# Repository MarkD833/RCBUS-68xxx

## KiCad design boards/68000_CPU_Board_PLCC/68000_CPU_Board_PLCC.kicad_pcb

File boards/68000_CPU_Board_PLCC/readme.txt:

DTACK Circuit:
==============
Silkscreen: It's 1,2,3 or 4 clocks NOT 2,4,8 or 16!

RCBus /RD & /WR signals:
========================
Possibly don't use /UDS or /LDS to gate the /RD or /WR signals.
Disconnect U4-8 from U5-13.
Connect U5-13 to +5V.

68000 R/W signal:
=================
This needs to go on the backplane as the 68681 needs the R/W signal
set before /CS is active.
Connect 68000 R/W signal (pin 9) to RCBus pin 35 (temporary fix).

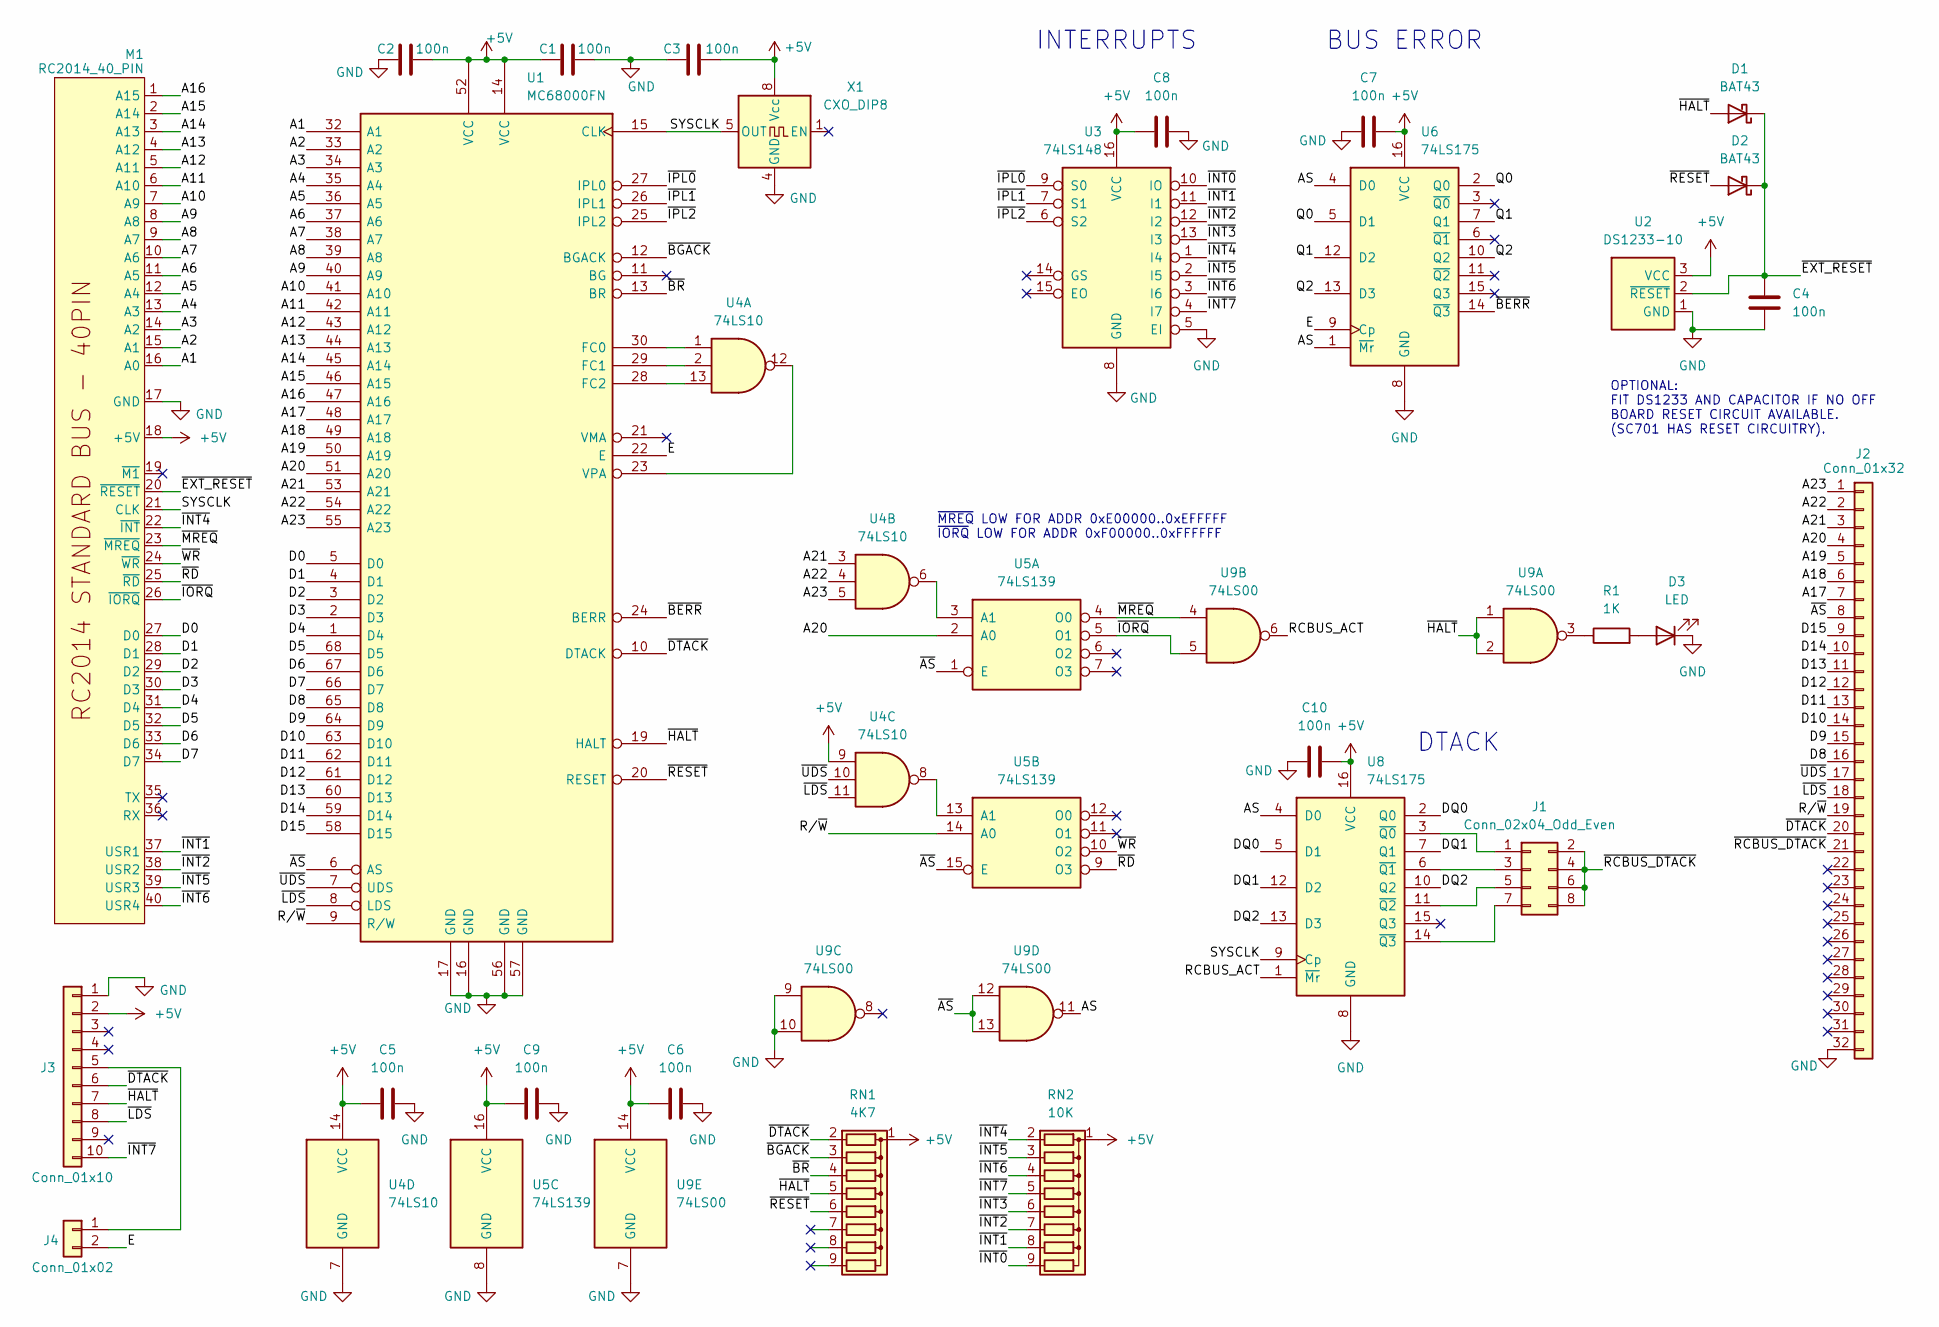
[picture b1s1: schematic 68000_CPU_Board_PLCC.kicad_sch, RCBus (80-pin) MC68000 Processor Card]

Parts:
C1, C2, C3, C4, C5, C6, C7, C8, C9, C10: 100n; C_Disc_D5.0mm_W2.5mm_P2.50mm
D1, D2: BAT43; D_DO-35_SOD27_P7.62mm_Horizontal
D3: LED; LED_D3.0mm
J1: Conn_02x04_Odd_Even; PinHeader_2x04_P2.54mm_Vertical
J2: Conn_01x32; PinSocket_1x32_P2.54mm_Vertical
J3: Conn_01x10; PinHeader_1x10_P2.54mm_Vertical
J4: Conn_01x02; PinHeader_1x02_P2.54mm_Vertical
M1: RC2014_40_PIN; RC2014_STD_40_PIN
R1: 1K; R_Axial_DIN0207_L6.3mm_D2.5mm_P7.62mm_Horizontal
RN1: 4K7; R_Array_SIP9
RN2: 10K; R_Array_SIP9
U1: MC68000FN; PLCC-68_THT-Socket
U2: DS1233-10; TO-92L_Inline
U3: 74LS148; DIP-16_W7.62mm_Socket
U4: 74LS10; DIP-14_W7.62mm_Socket
U5: 74LS139; DIP-16_W7.62mm_Socket
U6, U8: 74LS175; DIP-16_W7.62mm_Socket
U9: 74LS00; DIP-14_W7.62mm_Socket
X1: CXO_DIP8; Oscillator_DIP-8

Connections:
+5V: C1.1, C2.2, C3.2, C5.1, C6.1, C7.2, C8.1, C9.1, C10.2, J3.2, M1.18 (+5V), RN1.1 (common), RN2.1 (common), U1.14 (VCC), U1.52 (VCC), U2.3 (VCC), U3.16 (VCC), U4.9, U4.14 (VCC), U5.16 (VCC), U6.16 (VCC), U8.16 (VCC), U9.14 (VCC), X1.8 (Vcc)
/A1: M1.16 (A0), U1.32 (A1)
/A2: M1.15 (A1), U1.33 (A2)
/A3: M1.14 (A2), U1.34 (A3)
/A4: M1.13 (A3), U1.35 (A4)
/A5: M1.12 (A4), U1.36 (A5)
/A6: M1.11 (A5), U1.37 (A6)
/A7: M1.10 (A6), U1.38 (A7)
/A8: M1.9 (A7), U1.39 (A8)
/A9: M1.8 (A8), U1.40 (A9)
/A10: M1.7 (A9), U1.41 (A10)
/A11: M1.6 (A10), U1.42 (A11)
/A12: M1.5 (A11), U1.43 (A12)
/A13: M1.4 (A12), U1.44 (A13)
/A14: M1.3 (A13), U1.45 (A14)
/A15: M1.2 (A14), U1.46 (A15)
/A16: M1.1 (A15), U1.47 (A16)
/A17: J2.7, U1.48 (A17)
/A18: J2.6, U1.49 (A18)
/A19: J2.5, U1.50 (A19)
/A20: J2.4, U1.51 (A20), U5.2 (A0)
/A21: J2.3, U1.53 (A21), U4.3
/A22: J2.2, U1.54 (A22), U4.4
/A23: J2.1, U1.55 (A23), U4.5
/AS: U6.1 (~Mr), U6.4 (D0), U8.4 (D0), U9.11
/D0: M1.27 (D0), U1.5 (D0)
/D1: M1.28 (D1), U1.4 (D1)
/D2: M1.29 (D2), U1.3 (D2)
/D3: M1.30 (D3), U1.2 (D3)
/D4: M1.31 (D4), U1.1 (D4)
/D5: M1.32 (D5), U1.68 (D5)
/D6: M1.33 (D6), U1.67 (D6)
/D7: M1.34 (D7), U1.66 (D7)
/D8: J2.16, U1.65 (D8)
/D9: J2.15, U1.64 (D9)
/D10: J2.14, U1.63 (D10)
/D11: J2.13, U1.62 (D11)
/D12: J2.12, U1.61 (D12)
/D13: J2.11, U1.60 (D13)
/D14: J2.10, U1.59 (D14)
/D15: J2.9, U1.58 (D15)
/DQ0: U8.2 (Q0), U8.5 (D1)
/DQ1: U8.7 (Q1), U8.12 (D2)
/DQ2: U8.10 (Q2), U8.13 (D3)
/E: J4.2, U1.22 (E), U6.9 (Cp)
/Q0: U6.2 (Q0), U6.5 (D1)
/Q1: U6.7 (Q1), U6.12 (D2)
/Q2: U6.10 (Q2), U6.13 (D3)
/RCBUS_ACT: U8.1 (~Mr), U9.6
/R/~W: J2.19, U1.9 (R/W), U5.14 (A0)
/SYSCLK: M1.21 (CLK), U1.15 (CLK), U8.9 (Cp), X1.5 (OUT)
/~AS: J2.8, U1.6 (AS), U5.1 (E), U5.15 (E), U9.12, U9.13
/~BERR: U1.24 (BERR), U6.14 (~Q3)
/~BGACK: RN1.3 (R2), U1.12 (BGACK)
/~BR: RN1.4 (R3), U1.13 (BR)
/~DTACK: J2.20, J3.6, RN1.2 (R1), U1.10 (DTACK)
/~EXT_RESET: C4.1, D1.1 (K), D2.1 (K), M1.20 (~RESET), U2.2 (~RESET)
/~HALT: D1.2 (A), J3.7, RN1.5 (R4), U1.19 (HALT), U9.1, U9.2
/~INT0: RN2.9 (R8), U3.10 (IO)
/~INT1: M1.37 (USR1), RN2.8 (R7), U3.11 (I1)
/~INT2: M1.38 (USR2), RN2.7 (R6), U3.12 (I2)
/~INT3: RN2.6 (R5), U3.13 (I3)
/~INT4: M1.22 (~INT), RN2.2 (R1), U3.1 (I4)
/~INT5: M1.39 (USR3), RN2.3 (R2), U3.2 (I5)
/~INT6: M1.40 (USR4), RN2.4 (R3), U3.3 (I6)
/~INT7: J3.10, RN2.5 (R4), U3.4 (I7)
/~IORQ: M1.26 (~IORQ), U5.5 (O1), U9.5
/~IPL0: U1.27 (IPL0), U3.9 (S0)
/~IPL1: U1.26 (IPL1), U3.7 (S1)
/~IPL2: U1.25 (IPL2), U3.6 (S2)
/~LDS: J2.18, J3.8, U1.8 (LDS), U4.11
/~MREQ: M1.23 (~MREQ), U5.4 (O0), U9.4
/~RCBUS_DTACK: J1.2, J1.4, J1.6, J1.8, J2.21
/~RD: M1.25 (~RD), U5.9 (O3)
/~RESET: D2.2 (A), RN1.6 (R5), U1.20 (RESET)
/~UDS: J2.17, U1.7 (UDS), U4.10
/~WR: M1.24 (~WR), U5.10 (O2)
GND: C1.2, C2.1, C3.1, C4.2, C5.2, C6.2, C7.1, C8.2, C9.2, C10.1, D3.1 (K), J2.32, J3.1, M1.17 (GND), U1.16 (GND), U1.17 (GND), U1.56 (GND), U1.57 (GND), U2.1 (GND), U3.5 (EI), U3.8 (GND), U4.7 (GND), U5.8 (GND), U6.8 (GND), U8.8 (GND), U9.7 (GND), U9.9, U9.10, X1.4 (GND)
unnamed: D3.2 (A), R1.2
unnamed: J1.1, U8.3 (~Q0)
unnamed: J1.3, U8.6 (~Q1)
unnamed: J1.5, U8.11 (~Q2)
unnamed: J1.7, U8.14 (~Q3)
unnamed: J3.5, J4.1
unnamed: R1.1, U9.3
unnamed: U1.30 (FC0), U4.1
unnamed: U1.29 (FC1), U4.2
unnamed: U1.28 (FC2), U4.13
unnamed: U1.23 (VPA), U4.12
unnamed: U4.6, U5.3 (A1)
unnamed: U4.8, U5.13 (A1)

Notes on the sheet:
OPTIONAL: FIT DS1233 AND CAPACITOR IF NO OFF BOARD RESET CIRCUIT AVAILABLE. (SC701 HAS RESET CIRCUITRY).
INTERRUPTS
DTACK
~{MREQ} LOW FOR ADDR 0xE00000..0xEFFFFF ~{IORQ} LOW FOR ADDR 0xF00000..0xFFFFFF
BUS ERROR

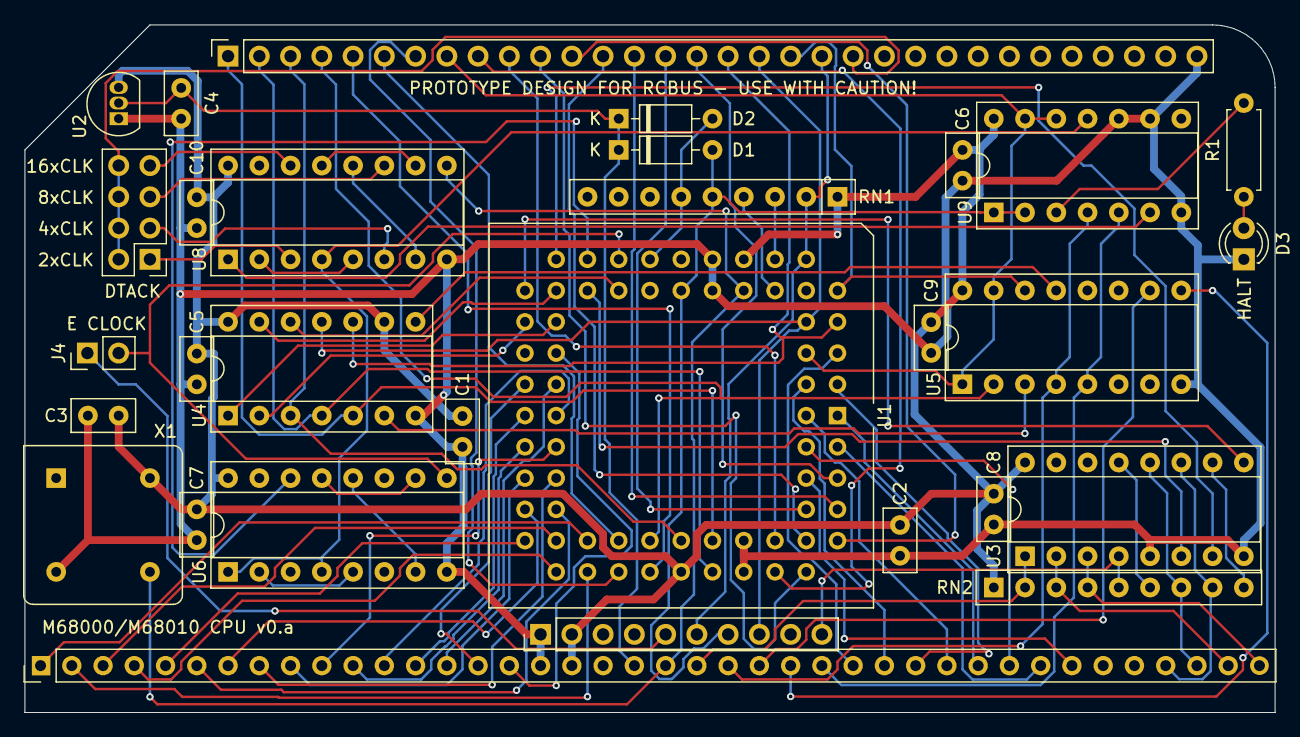
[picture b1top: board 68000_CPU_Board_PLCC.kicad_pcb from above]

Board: 2 copper layers, 101.6 x 55.9 mm, 30 parts (0 on the bottom side), 91 nets.

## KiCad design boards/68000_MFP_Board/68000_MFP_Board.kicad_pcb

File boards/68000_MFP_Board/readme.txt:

Thoughts:
=========
+ Should the MFPs each have their own choice of interrupt level?

Physical Board
==============
+ Experiment to find the maximum width of board that JLCPCB will accept to keep the
  low price.
+ Modify the RCBus80 medium board footprint in Kicad so that pins 1,40,41 & 80 don't
  throw DRC warnings/errors.

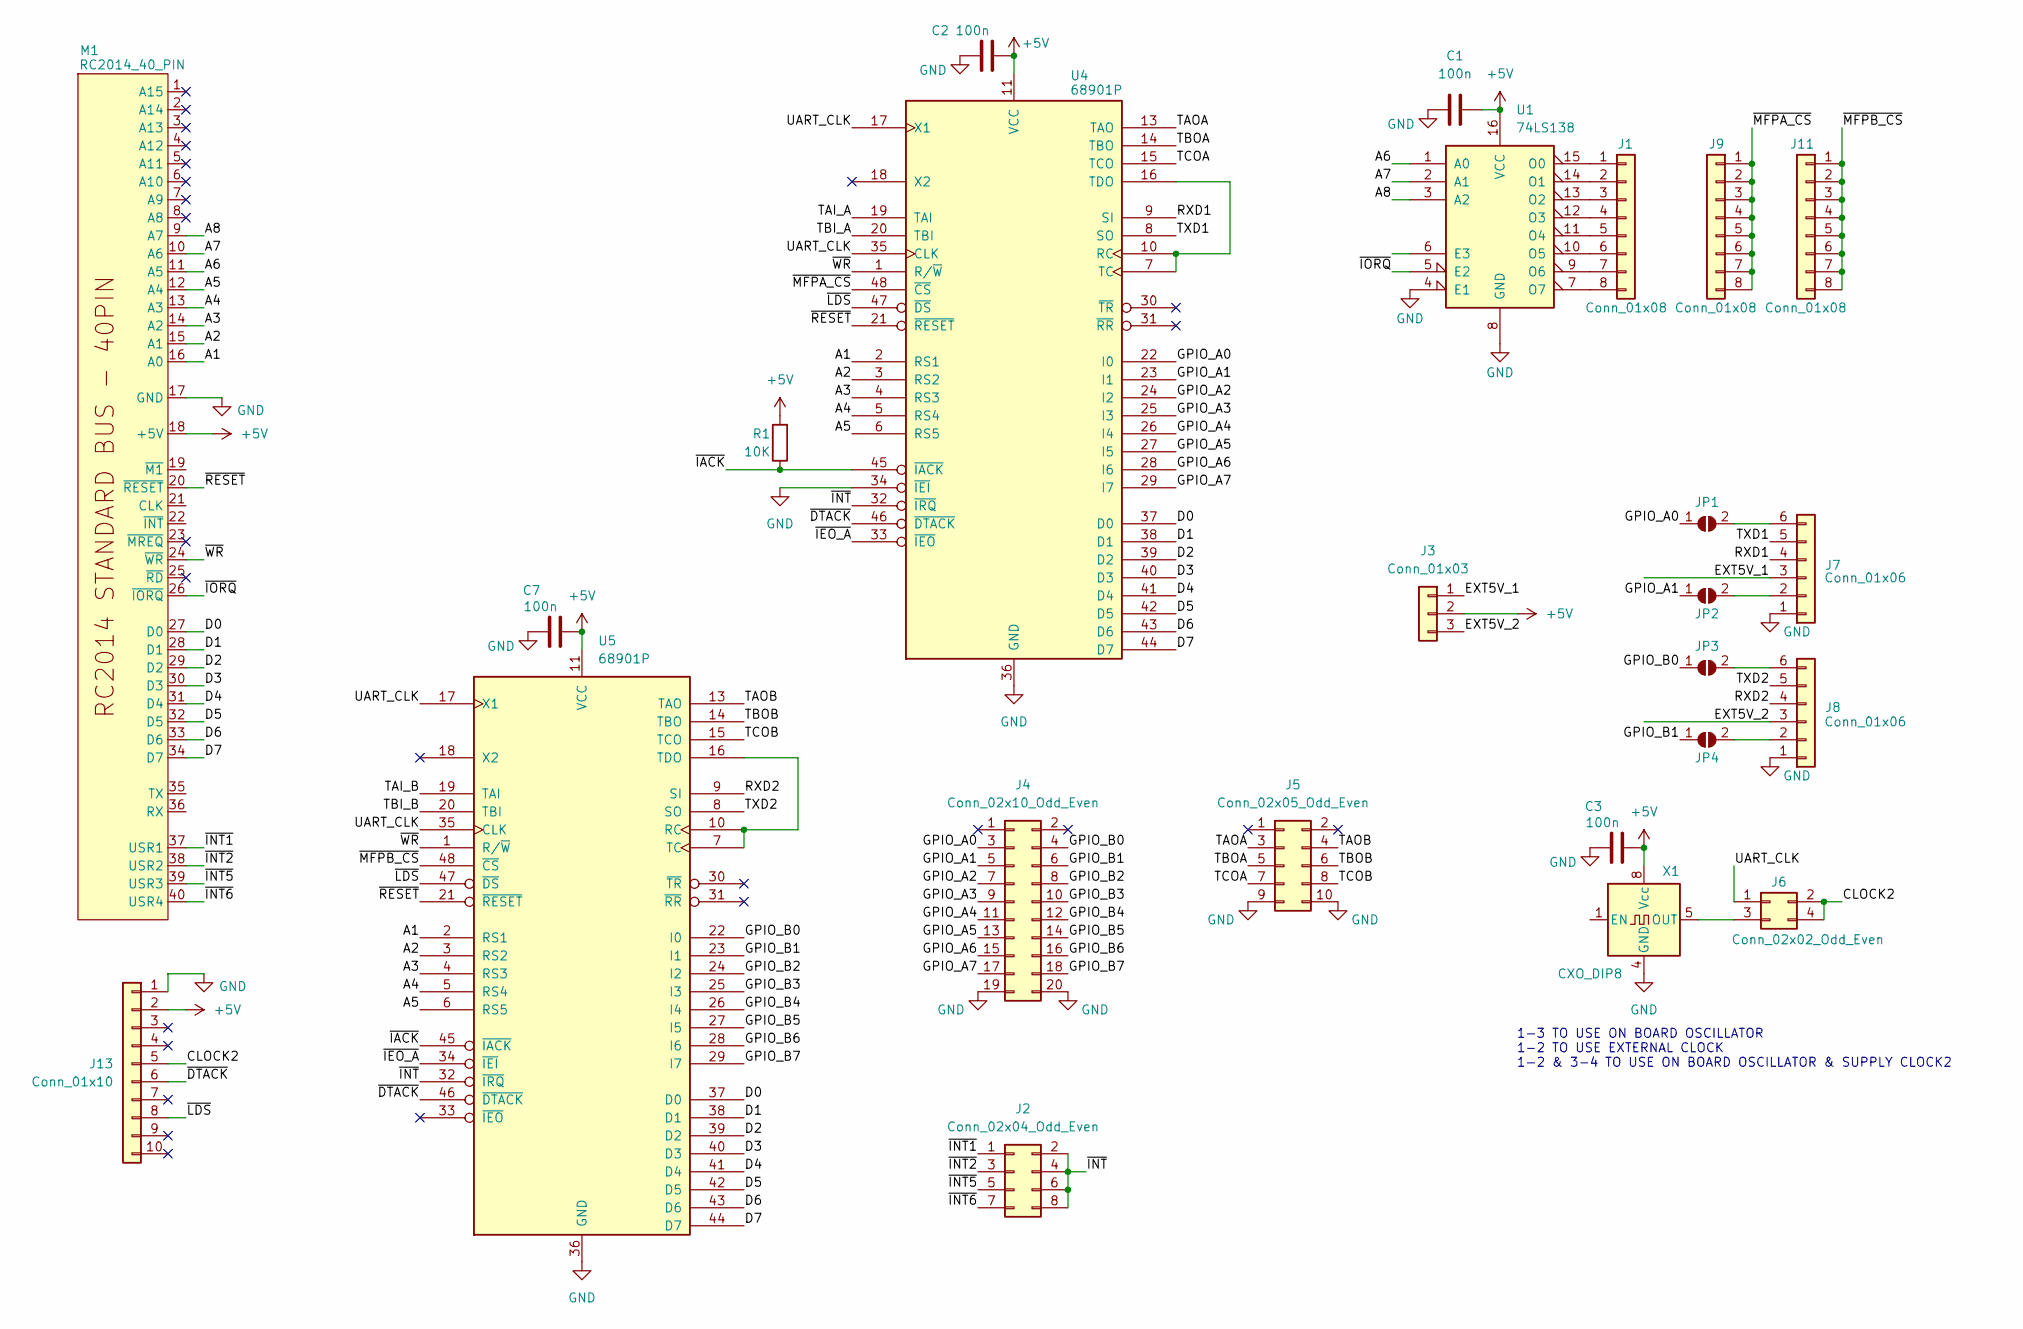
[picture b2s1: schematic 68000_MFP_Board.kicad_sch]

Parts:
C1, C2, C3, C7: 100n; C_Disc_D5.0mm_W2.5mm_P2.50mm
J1, J9, J11: Conn_01x08; PinHeader_1x08_P2.54mm_Vertical
J2: Conn_02x04_Odd_Even; PinHeader_2x04_P2.54mm_Vertical
J3: Conn_01x03; PinHeader_1x03_P2.54mm_Vertical
J4: Conn_02x10_Odd_Even; PinHeader_2x10_P2.54mm_Horizontal
J5: Conn_02x05_Odd_Even; PinHeader_2x05_P2.54mm_Horizontal
J6: Conn_02x02_Odd_Even; PinHeader_2x02_P2.54mm_Vertical
J7, J8: Conn_01x06; PinSocket_1x06_P2.54mm_Horizontal
J13: Conn_01x10; PinHeader_1x10_P2.54mm_Vertical
JP1, JP2, JP3, JP4: SolderJumper; SolderJumper-2_P1.3mm_Open_Pad1.0x1.5mm
M1: RC2014_40_PIN; RC2014_STD_40_PIN
R1: 10K; R_Axial_DIN0207_L6.3mm_D2.5mm_P7.62mm_Horizontal
U1: 74LS138; DIP-16_W7.62mm_Socket
U4, U5: 68901P; DIP-48_W15.24mm_Socket
X1: CXO_DIP8; Oscillator_DIP-8

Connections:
+5V: C1.2, C2.2, C3.2, C7.2, J3.2, J13.2, M1.18 (+5V), R1.2, U1.16 (VCC), U4.11 (VCC), U5.11 (VCC), X1.8 (Vcc)
/A1: M1.16 (A0), U4.2 (RS1), U5.2 (RS1)
/A2: M1.15 (A1), U4.3 (RS2), U5.3 (RS2)
/A3: M1.14 (A2), U4.4 (RS3), U5.4 (RS3)
/A4: M1.13 (A3), U4.5 (RS4), U5.5 (RS4)
/A5: M1.12 (A4), U4.6 (RS5), U5.6 (RS5)
/A6: M1.11 (A5), U1.1 (A0)
/A7: M1.10 (A6), U1.2 (A1)
/A8: M1.9 (A7), U1.3 (A2)
/CLOCK2: J6.2, J6.4, J13.5
/D0: M1.27 (D0), U4.37 (D0), U5.37 (D0)
/D1: M1.28 (D1), U4.38 (D1), U5.38 (D1)
/D2: M1.29 (D2), U4.39 (D2), U5.39 (D2)
/D3: M1.30 (D3), U4.40 (D3), U5.40 (D3)
/D4: M1.31 (D4), U4.41 (D4), U5.41 (D4)
/D5: M1.32 (D5), U4.42 (D5), U5.42 (D5)
/D6: M1.33 (D6), U4.43 (D6), U5.43 (D6)
/D7: M1.34 (D7), U4.44 (D7), U5.44 (D7)
/EXT5V_1: J3.1, J7.3
/EXT5V_2: J3.3, J8.3
/GPIO_A0: J4.3, JP1.1 (A), U4.22 (I0)
/GPIO_A1: J4.5, JP2.1 (A), U4.23 (I1)
/GPIO_A2: J4.7, U4.24 (I2)
/GPIO_A3: J4.9, U4.25 (I3)
/GPIO_A4: J4.11, U4.26 (I4)
/GPIO_A5: J4.13, U4.27 (I5)
/GPIO_A6: J4.15, U4.28 (I6)
/GPIO_A7: J4.17, U4.29 (I7)
/GPIO_B0: J4.4, JP3.1 (A), U5.22 (I0)
/GPIO_B1: J4.6, JP4.1 (A), U5.23 (I1)
/GPIO_B2: J4.8, U5.24 (I2)
/GPIO_B3: J4.10, U5.25 (I3)
/GPIO_B4: J4.12, U5.26 (I4)
/GPIO_B5: J4.14, U5.27 (I5)
/GPIO_B6: J4.16, U5.28 (I6)
/GPIO_B7: J4.18, U5.29 (I7)
/RXD1: J7.4, U4.9 (SI)
/RXD2: J8.4, U5.9 (SI)
/TAI_A: U4.19 (TAI)
/TAI_B: U5.19 (TAI)
/TAOA: J5.3, U4.13 (TAO)
/TAOB: J5.4, U5.13 (TAO)
/TBI_A: U4.20 (TBI)
/TBI_B: U5.20 (TBI)
/TBOA: J5.5, U4.14 (TBO)
/TBOB: J5.6, U5.14 (TBO)
/TCOA: J5.7, U4.15 (TCO)
/TCOB: J5.8, U5.15 (TCO)
/TXD1: J7.5, U4.8 (SO)
/TXD2: J8.5, U5.8 (SO)
/UART_CLK: J6.1, U4.17 (X1), U4.35 (CLK), U5.17 (X1), U5.35 (CLK)
/~DTACK: J13.6, U4.46 (~DTACK), U5.46 (~DTACK)
/~IACK: R1.1, U4.45 (~IACK), U5.45 (~IACK)
/~IEO_A: U4.33 (~IEO), U5.34 (~IEI)
/~INT1: J2.1, M1.37 (USR1)
/~INT2: J2.3, M1.38 (USR2)
/~INT5: J2.5, M1.39 (USR3)
/~INT6: J2.7, M1.40 (USR4)
/~INT: J2.2, J2.4, J2.6, J2.8, U4.32 (~IRQ), U5.32 (~IRQ)
/~IORQ: M1.26 (~IORQ), U1.5 (E2)
/~LDS: J13.8, U4.47 (~DS), U5.47 (~DS)
/~MFPA_CS: J9.1, J9.2, J9.3, J9.4, J9.5, J9.6, J9.7, J9.8, U4.48 (~CS)
/~MFPB_CS: J11.1, J11.2, J11.3, J11.4, J11.5, J11.6, J11.7, J11.8, U5.48 (~CS)
/~RESET: M1.20 (~RESET), U4.21 (~RESET), U5.21 (~RESET)
/~WR: M1.24 (~WR), U4.1 (R/~W), U5.1 (R/~W)
GND: C1.1, C2.1, C3.1, C7.1, J4.19, J4.20, J5.9, J5.10, J7.1, J8.1, J13.1, M1.17 (GND), U1.4 (E1), U1.8 (GND), U4.34 (~IEI), U4.36 (GND), U5.36 (GND), X1.4 (GND)
unnamed: J1.1, U1.15 (O0)
unnamed: J1.2, U1.14 (O1)
unnamed: J1.3, U1.13 (O2)
unnamed: J1.4, U1.12 (O3)
unnamed: J1.5, U1.11 (O4)
unnamed: J1.6, U1.10 (O5)
unnamed: J1.7, U1.9 (O6)
unnamed: J1.8, U1.7 (O7)
unnamed: J6.3, X1.5 (OUT)
unnamed: J7.2, JP2.2 (B)
unnamed: J7.6, JP1.2 (B)
unnamed: J8.2, JP4.2 (B)
unnamed: J8.6, JP3.2 (B)
unnamed: U4.7 (TC), U4.10 (RC), U4.16 (TDO)
unnamed: U5.7 (TC), U5.10 (RC), U5.16 (TDO)

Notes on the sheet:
1-3 TO USE ON BOARD OSCILLATOR 1-2 TO USE EXTERNAL CLOCK 1-2 & 3-4 TO USE ON BOARD OSCILLATOR & SUPPLY CLOCK2

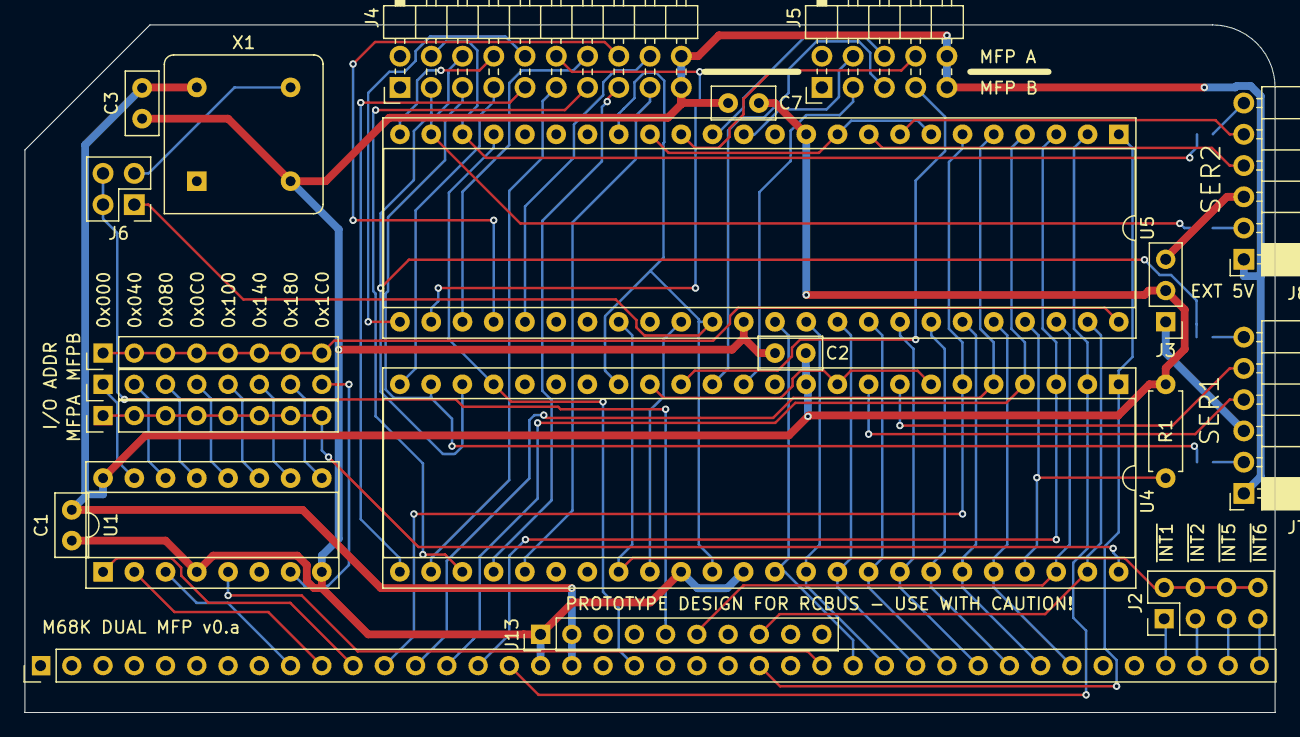
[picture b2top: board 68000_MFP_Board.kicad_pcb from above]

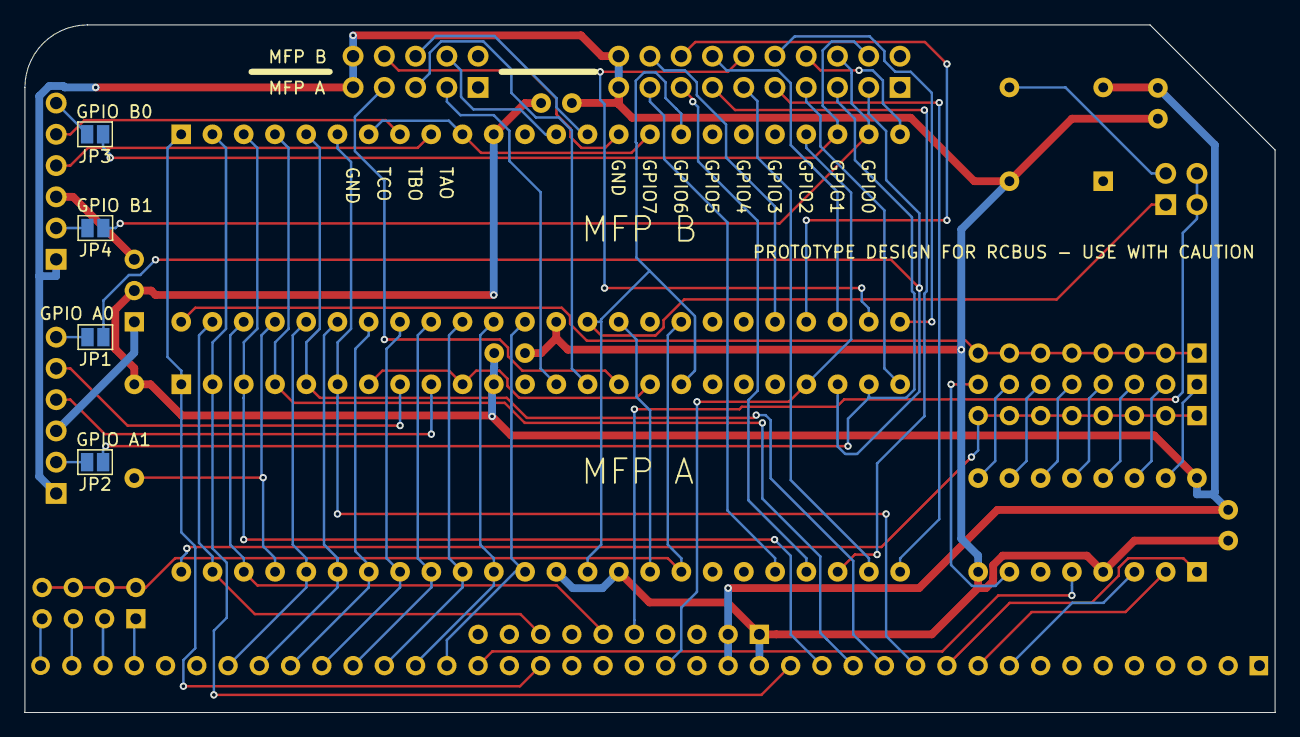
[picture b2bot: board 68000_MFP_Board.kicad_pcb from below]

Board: 2 copper layers, 101.6 x 55.9 mm, 25 parts (4 on the bottom side), 77 nets.

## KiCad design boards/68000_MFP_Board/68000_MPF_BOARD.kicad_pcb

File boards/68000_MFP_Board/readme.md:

# Dual MultiFunction Peripheral Board

# Details
The multifunction peripheral board is populated with two 68901 chips. Both chips do not have to be fitted. The board will work with just one chip fitted.

## Address Decoding
The address decoding is carried out by a 74LS688 combined with a 74LS138 to generate 8 separate 2048 byte blocks residing between addresses $D10000 and $D13FFF.

The base address of each MFP is determined by the placement of a jumper between adjacent pins on J12 & J9 (MFP A) and J12 & J11 (MFP B).

## Device Register Access
The registers of the MFP are 8 bits wide and are accessed on consecutive ODD addresses from the base address set by the address decode logic. Assuming that the /CS0 jumper has been fitted for MFP #1, then the first few registers are accessed on the following addresses:
+ $D10001 : General Purpose I/O Data Register
+ $D10003 : Active Edge Register
+ $D10005 : Data Direction Register

## DTACK
Each MFP generates its own /DTACK signal internally which is then routed back to the processor via RCBus-80 pin 62.

## Clock Source
The clock signal for the chip functions and timers can be sourced from the on board 3.6864MHz crystal oscillator (X1 in the schematic) or from an external clock source on the RCBus-80 CLOCK2 pin (pin 61) via the jumper J6.

Note that each MFP chip **requires** a clock signal in order to function correctly, even if the UART and timer are not being used. 

## UART Baud Rate Clock
The MFP does not have a built-in baud rate generator like the 68681 does. In order to generate the required UART clock, the output of timer D hard wired to the Tx and Rx clock inputs.

Assuming that the crystal oscillator (or CLOCK2) frequency is 3.6864MHz, with the prescaled set to DIV 4 and the required baud rate of 9600 baud, then the following calculation will provide the timer D reload value:
```
reload value = clock / prescaler / 16 / baud rate
reload value = 3686400 / 4 / 16 / 9600 = 6
```

## UART Edge Connector
The 6-pin UART connector is compatible with an FTDI USB-TTL Serial interface board.

## UART Flow Control
Serial hardware flow control can be achieved on the serial port by shorting the appropriate solder jumpers on the rear of the board. This routes the 2 flow control signals for each serial port to 2 I/O pins one each MFT.

## Input / Output Pins
Each MFP provides a single 8-bit I/O port with programmable direction control for each bit. Connector J4 carries the 8 port pins for both MFP chips as well as 2 GND pins.

Note that the board **does not have** any protection built in to prevent damage to the MFP chips if one of these pins is mis-used.

## Power
The complete RCBus system can be powered from the 5V pin of one of the USB-TTL serial connectors by fitting a jumper in place on the appropriate pins of J3.

Note that there is a current limit of 500mA - imposed by the host system USB hardware - when the system is powered this way. It is relatively easy to exceed this limit once several boards are in use and I recommend that the system be powered from an external 5V supply connected to the RCBus backplane instead.

# Board Assembly
Assembly of the board should be fairly straightforward as there are no surface mount devices to deal with.

If you choose have a turned pin socket for the system clock, then an 8-pin DIL turned pin socket can be used. I flipped the socket over - pins pointing upwards - and easily pushed out pins 2,3,6 & 7.

When fitting the 80-pin right angle connector, initially only solder a couple of pins at opposite ends of the connector so that you can make any adjustments if the board is not vertical when fitted to the backplane.

Note the orientation of the two MFP chips - they are effectively upside down.

# Jumpers
+ J2: Specify the interupt line to be shared by the MFP chips
  + 1-2 : use /INT1
  + 3-4 : use /INT2
  + 5-6 : use /INT5
  + 7-8 : use /INT6 
+ J3: (**only fit one jumper** if not using an external 5V power source)
  + 1-2 : Power the system from the USB-TTL Serial board on Serial #1
  + 2-3 : Power the system from the USB-TTL Serial board on Serial #2
+ J4: I/O pins for both MFP chips - refer to schematic
+ J5: Timer A, B & C outputs for both MFP chips - refer to schematic
+ J6: Specify the clock source
  + 1-3 Use the onboard clock source
  + 1-2 Use the RCBus clock source from CLOCK2
  + 1-2 *and* 3-4: Use the onboard clock source and supply the RCBus CLOCK2 signal with the clock.
+ J7: Serial #1 port
+ J8: Serial #2 port
+ J9 (with J12): Specify the IO Address for MFP chip A
+ J11 (with J12): Specify the IO Address for MFP chip B
+ J12: IO Address selection
  + $D10000
  + $D10800
  + $D11000
  + $D11800
  + $D12000
  + $D12800
  + $D13000
  + $D13800
+ J14: Timer A & B inputs - refer to schematic

# Caution
Pay attention to the orientation of the chips on this board.

# Errors
None so far.

# Thoughts / Enhancements
+ Should the MFPs each have their own choice of interrupt level?

# To Do
+ Experiment to find the maximum width of board that JLCPCB will accept to keep the low price.
+ Modify the RCBus80 medium board footprint in Kicad so that pins 1,40,41 & 80 don't throw DRC warnings/errors.

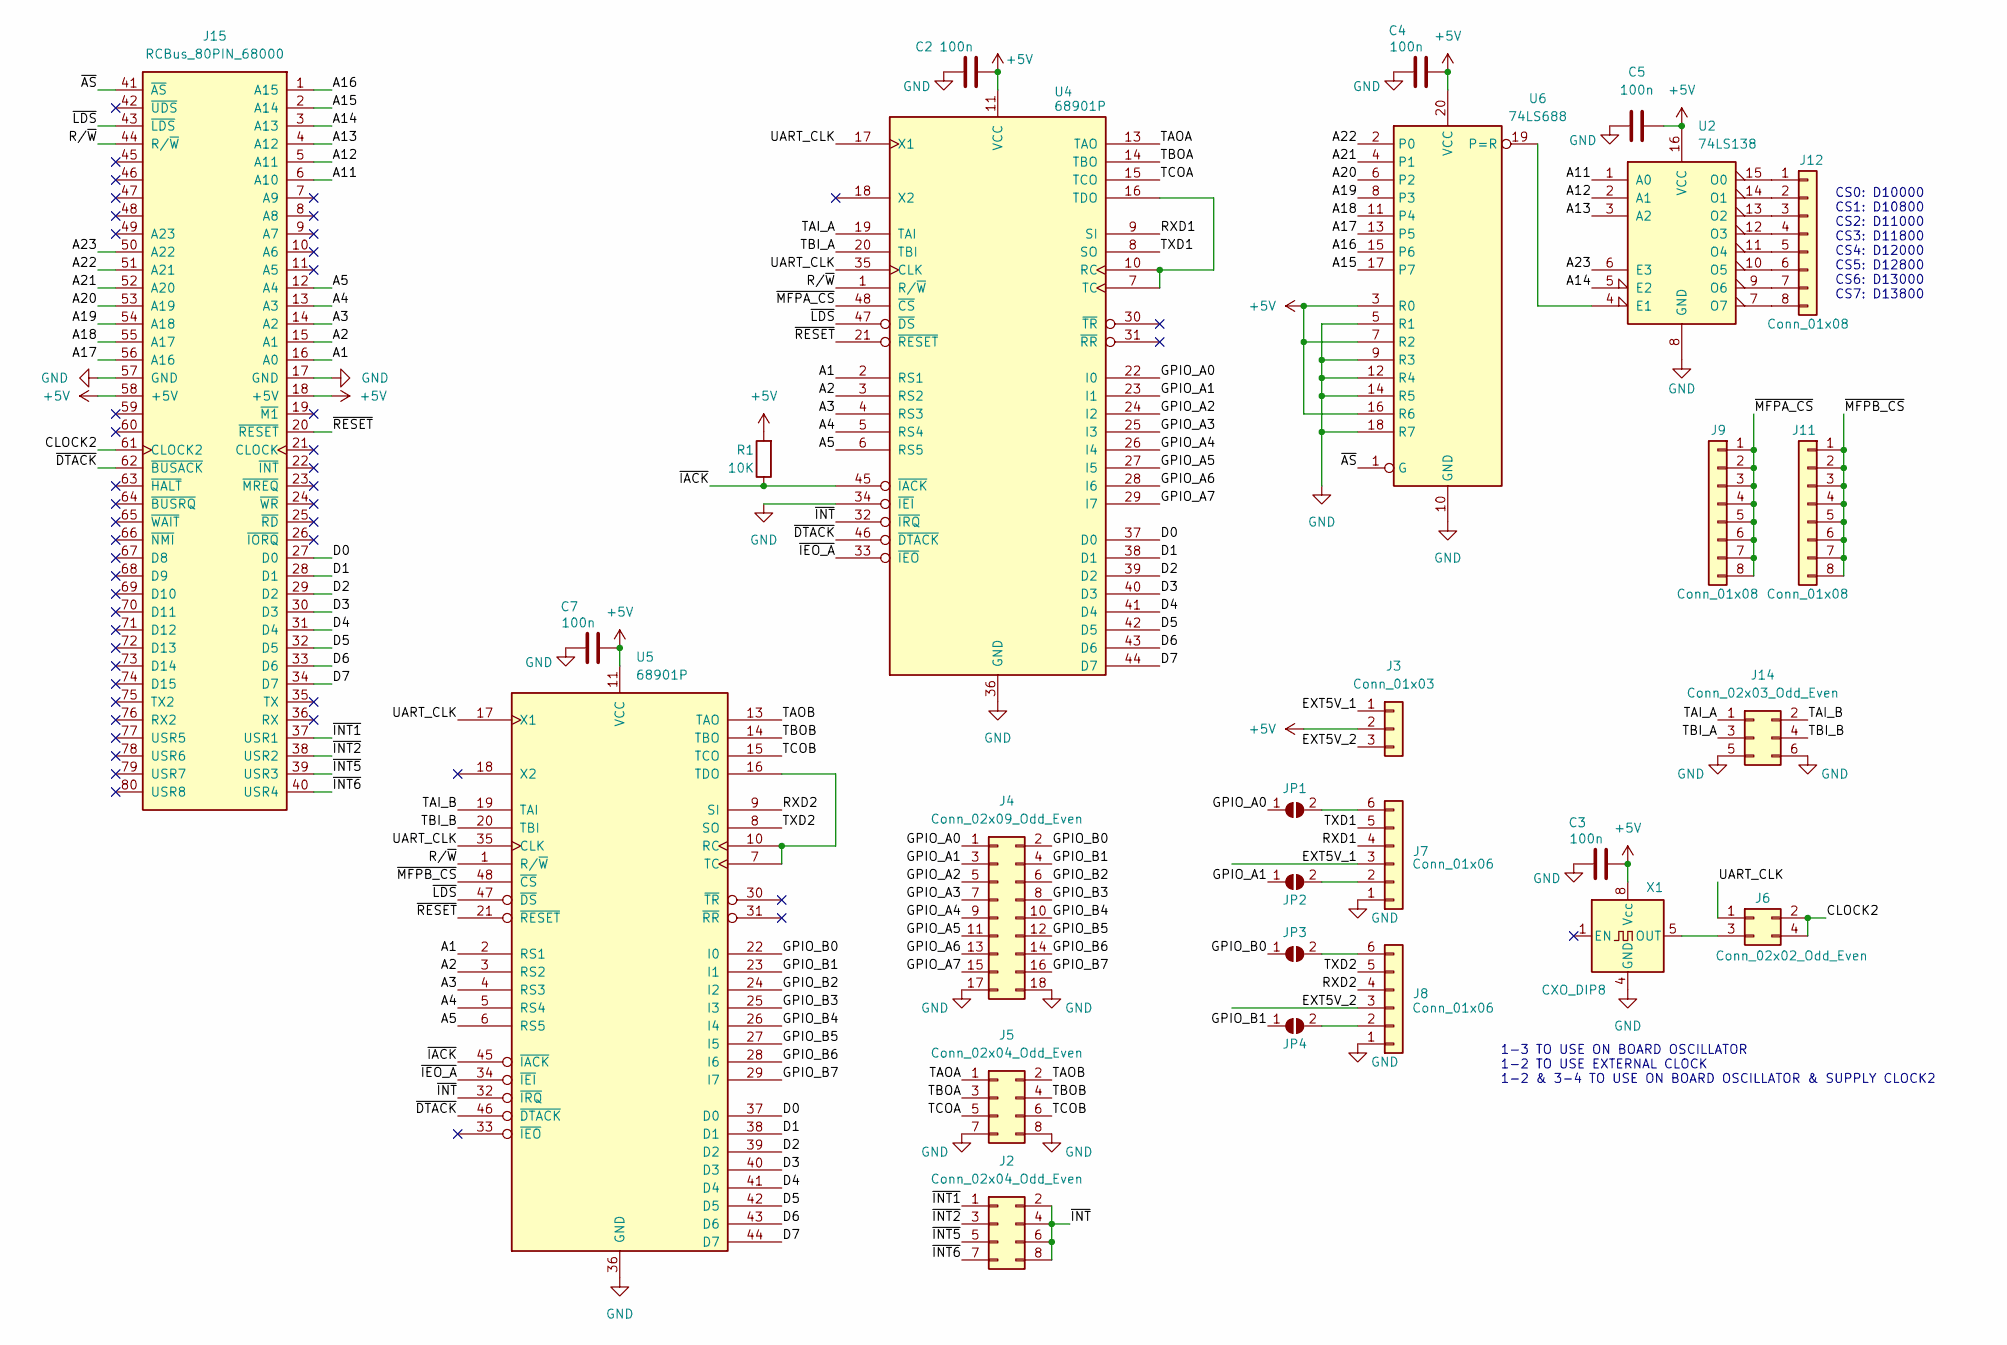
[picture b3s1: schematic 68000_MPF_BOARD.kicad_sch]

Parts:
C2, C3, C4, C5, C7: 100n; C_Disc_D5.0mm_W2.5mm_P2.50mm
J2, J5: Conn_02x04_Odd_Even; PinHeader_2x04_P2.54mm_Vertical
J3: Conn_01x03; PinHeader_1x03_P2.54mm_Vertical
J4: Conn_02x09_Odd_Even; PinHeader_2x09_P2.54mm_Vertical
J6: Conn_02x02_Odd_Even; PinHeader_2x02_P2.54mm_Vertical
J7, J8: Conn_01x06; PinSocket_1x06_P2.54mm_Horizontal
J9, J11, J12: Conn_01x08; PinHeader_1x08_P2.54mm_Vertical
J14: Conn_02x03_Odd_Even; PinHeader_2x03_P2.54mm_Vertical
J15: RCBus_80PIN_68000; RCBus_80p_Medium
JP1, JP2, JP3, JP4: SolderJumper; SolderJumper-2_P1.3mm_Open_Pad1.0x1.5mm
R1: 10K; R_Axial_DIN0207_L6.3mm_D2.5mm_P7.62mm_Horizontal
U2: 74LS138; DIP-16_W7.62mm_Socket
U4, U5: 68901P; DIP-48_W15.24mm_Socket
U6: 74LS688; DIP-20_W7.62mm_Socket
X1: CXO_DIP8; Oscillator_DIP-8

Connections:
+5V: C2.2, C3.2, C4.2, C5.2, C7.2, J3.2, J15.18 (+5V), J15.58 (+5V), R1.2, U2.16 (VCC), U4.11 (VCC), U5.11 (VCC), U6.3 (R0), U6.7 (R2), U6.16 (R6), U6.20 (VCC), X1.8 (Vcc)
/A1: J15.16 (A0), U4.2 (RS1), U5.2 (RS1)
/A2: J15.15 (A1), U4.3 (RS2), U5.3 (RS2)
/A3: J15.14 (A2), U4.4 (RS3), U5.4 (RS3)
/A4: J15.13 (A3), U4.5 (RS4), U5.5 (RS4)
/A5: J15.12 (A4), U4.6 (RS5), U5.6 (RS5)
/A11: J15.6 (A10), U2.1 (A0)
/A12: J15.5 (A11), U2.2 (A1)
/A13: J15.4 (A12), U2.3 (A2)
/A14: J15.3 (A13), U2.5 (E2)
/A15: J15.2 (A14), U6.17 (P7)
/A16: J15.1 (A15), U6.15 (P6)
/A17: J15.56 (A16), U6.13 (P5)
/A18: J15.55 (A17), U6.11 (P4)
/A19: J15.54 (A18), U6.8 (P3)
/A20: J15.53 (A19), U6.6 (P2)
/A21: J15.52 (A20), U6.4 (P1)
/A22: J15.51 (A21), U6.2 (P0)
/A23: J15.50 (A22), U2.6 (E3)
/CLOCK2: J6.2, J6.4, J15.61 (CLOCK2)
/D0: J15.27 (D0), U4.37 (D0), U5.37 (D0)
/D1: J15.28 (D1), U4.38 (D1), U5.38 (D1)
/D2: J15.29 (D2), U4.39 (D2), U5.39 (D2)
/D3: J15.30 (D3), U4.40 (D3), U5.40 (D3)
/D4: J15.31 (D4), U4.41 (D4), U5.41 (D4)
/D5: J15.32 (D5), U4.42 (D5), U5.42 (D5)
/D6: J15.33 (D6), U4.43 (D6), U5.43 (D6)
/D7: J15.34 (D7), U4.44 (D7), U5.44 (D7)
/EXT5V_1: J3.1, J7.3
/EXT5V_2: J3.3, J8.3
/GPIO_A0: J4.1, JP1.1 (A), U4.22 (I0)
/GPIO_A1: J4.3, JP2.1 (A), U4.23 (I1)
/GPIO_A2: J4.5, U4.24 (I2)
/GPIO_A3: J4.7, U4.25 (I3)
/GPIO_A4: J4.9, U4.26 (I4)
/GPIO_A5: J4.11, U4.27 (I5)
/GPIO_A6: J4.13, U4.28 (I6)
/GPIO_A7: J4.15, U4.29 (I7)
/GPIO_B0: J4.2, JP3.1 (A), U5.22 (I0)
/GPIO_B1: J4.4, JP4.1 (A), U5.23 (I1)
/GPIO_B2: J4.6, U5.24 (I2)
/GPIO_B3: J4.8, U5.25 (I3)
/GPIO_B4: J4.10, U5.26 (I4)
/GPIO_B5: J4.12, U5.27 (I5)
/GPIO_B6: J4.14, U5.28 (I6)
/GPIO_B7: J4.16, U5.29 (I7)
/RXD1: J7.4, U4.9 (SI)
/RXD2: J8.4, U5.9 (SI)
/R/~W: J15.44 (R/~W), U4.1 (R/~W), U5.1 (R/~W)
/TAI_A: J14.1, U4.19 (TAI)
/TAI_B: J14.2, U5.19 (TAI)
/TAOA: J5.1, U4.13 (TAO)
/TAOB: J5.2, U5.13 (TAO)
/TBI_A: J14.3, U4.20 (TBI)
/TBI_B: J14.4, U5.20 (TBI)
/TBOA: J5.3, U4.14 (TBO)
/TBOB: J5.4, U5.14 (TBO)
/TCOA: J5.5, U4.15 (TCO)
/TCOB: J5.6, U5.15 (TCO)
/TXD1: J7.5, U4.8 (SO)
/TXD2: J8.5, U5.8 (SO)
/UART_CLK: J6.1, U4.17 (X1), U4.35 (CLK), U5.17 (X1), U5.35 (CLK)
/~AS: J15.41 (~AS), U6.1 (G)
/~DTACK: J15.62 (~BUSACK), U4.46 (~DTACK), U5.46 (~DTACK)
/~IACK: R1.1, U4.45 (~IACK), U5.45 (~IACK)
/~IEO_A: U4.33 (~IEO), U5.34 (~IEI)
/~INT1: J2.1, J15.37 (USR1)
/~INT2: J2.3, J15.38 (USR2)
/~INT5: J2.5, J15.39 (USR3)
/~INT6: J2.7, J15.40 (USR4)
/~INT: J2.2, J2.4, J2.6, J2.8, U4.32 (~IRQ), U5.32 (~IRQ)
/~LDS: J15.43 (~LDS), U4.47 (~DS), U5.47 (~DS)
/~MFPA_CS: J9.1, J9.2, J9.3, J9.4, J9.5, J9.6, J9.7, J9.8, U4.48 (~CS)
/~MFPB_CS: J11.1, J11.2, J11.3, J11.4, J11.5, J11.6, J11.7, J11.8, U5.48 (~CS)
/~RESET: J15.20 (~RESET), U4.21 (~RESET), U5.21 (~RESET)
GND: C2.1, C3.1, C4.1, C5.1, C7.1, J4.17, J4.18, J5.7, J5.8, J7.1, J8.1, J14.5, J14.6, J15.17 (GND), J15.57 (GND), U2.8 (GND), U4.34 (~IEI), U4.36 (GND), U5.36 (GND), U6.5 (R1), U6.9 (R3), U6.10 (GND), U6.12 (R4), U6.14 (R5), U6.18 (R7), X1.4 (GND)
unnamed: J6.3, X1.5 (OUT)
unnamed: J7.2, JP2.2 (B)
unnamed: J7.6, JP1.2 (B)
unnamed: J8.2, JP4.2 (B)
unnamed: J8.6, JP3.2 (B)
unnamed: J12.1, U2.15 (O0)
unnamed: J12.2, U2.14 (O1)
unnamed: J12.3, U2.13 (O2)
unnamed: J12.4, U2.12 (O3)
unnamed: J12.5, U2.11 (O4)
unnamed: J12.6, U2.10 (O5)
unnamed: J12.7, U2.9 (O6)
unnamed: J12.8, U2.7 (O7)
unnamed: U2.4 (E1), U6.19 (P=R)
unnamed: U4.7 (TC), U4.10 (RC), U4.16 (TDO)
unnamed: U5.7 (TC), U5.10 (RC), U5.16 (TDO)

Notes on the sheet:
1-3 TO USE ON BOARD OSCILLATOR 1-2 TO USE EXTERNAL CLOCK 1-2 & 3-4 TO USE ON BOARD OSCILLATOR & SUPPLY CLOCK2
CS0: D10000 CS1: D10800 CS2: D11000 CS3: D11800 CS4: D12000 CS5: D12800 CS6: D13000 CS7: D13800
